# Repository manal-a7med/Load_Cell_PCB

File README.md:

# Load_Cell_PCB
HX711 Load Cell PCB Design using KiCAD 10.0

Manal Ahmed Matheen
ELECTRONICS ASSIGNMENT REPORT
Automated Food Dispensing System — Load Cell Measurement Subsystem

Task	Design Problem Statement
Domain	Embedded Systems / PCB Design
Status	Internship Technical Submission
Date	31 March 2026

Task 1 — Load Cell Selection and Key Specifications

The load cell is the primary transducer in this food dispensing system. It converts the mechanical force (weight of dispensed food) into an electrical signal. Choosing the right load cell is critical for accuracy, durability, and noise immunity in an industrial or semi-industrial environment.

1.1 Recommended Load Cell — Recommendation

✔ Selected	HX711-compatible Single-Point Load Cell (e.g., TAL220B / CZL635 / Bosche H40A) — Strain-gauge type, single-point platform cell

Reason	Strain-gauge load cells offer excellent linearity, low hysteresis, and are widely compatible with 24-bit ADC front-ends. Single-point cells are ideal for platform-style food-pan weighing.

1.2 Key Specifications to Consider

A. Load Capacity
•	Select rated capacity based on maximum expected food load plus a 20–30% safety margin.
•	For a food dispenser pan: 1 kg to 5 kg rated capacity is typical (e.g., 5 kg full-scale).
•	Overload protection rating should be ≥150% of rated capacity to survive mechanical disturbances.

B. Accuracy & Linearity
Specification targets for a reliable food-dispensing system:

Specification	Typical Requirement	Recommended Value
Non-linearity	< ±0.05% FS	< ±0.02% FS
Hysteresis	< ±0.05% FS	< ±0.02% FS
Repeatability	< ±0.05% FS	< ±0.01% FS
Temperature Effect (Zero)	< ±0.03% FS/°C	< ±0.02% FS/°C
Creep (30 min)	< ±0.03% FS	< ±0.02% FS

C. Sensitivity & Output
•	Standard bridge sensitivity: 1–3 mV/V (e.g., 2 mV/V at full rated load).
•	Bridge excitation voltage: 5V or 10V (match to ADC front-end supply).
•	Higher sensitivity = better SNR before amplification.

D. Resistance to Mechanical Disturbances
•	IP Rating: Minimum IP54 for food/dust environments; IP65 preferred.
•	Material: Aluminium alloy body (anodised) for food-grade applications; stainless steel for wet wash-down.
•	Mechanical shock rating: ≥10g or higher to withstand dispensing impacts.
•	Anti-vibration: Use rubber mounting isolators under the cell to decouple conveyor/motor vibration.

E. Electrical Noise Immunity
•	Use a 4-wire (Wheatstone bridge) or 6-wire load cell for remote sense compensation.
•	Shield the signal cable and connect the shield to a single-point earth at the MCU side.
•	Digital filtering in firmware (moving average / IIR) to suppress 50 Hz mains interference.

1.3 Comparative Summary of Load Cell Types

Type	Pros	Cons	Suitability
Strain Gauge (Single Point)	Low cost, compact, good linearity	Sensitive to off-center loads beyond cell rating	✔ Best for this application
Strain Gauge (Bending Beam)	High accuracy, robust	Larger footprint	Good alternative
Capacitive	No hysteresis, very accurate	Complex electronics, higher cost	Overkill for this use
Piezoelectric	Fast dynamic response	Cannot measure static weight accurately	✘ Not suitable

Task 2 — ADC Selection for Load Cell Signal Acquisition

Load cell output signals are extremely small (millivolt-range differential signals). A high-resolution, low-noise ADC with an integrated instrumentation amplifier front-end is required. The ADC communicates directly with the MCU.

2.1 Recommended ADC — HX711

✔ Selected	HX711 — 24-bit Sigma-Delta ADC with integrated PGA (Programmable Gain Amplifier), purpose-built for load cell / Wheatstone bridge applications

2.2 HX711 Key Specifications

Parameter	Value
Resolution	24-bit (≈16 million counts)
Input Channels	2 differential inputs (A and B)
Programmable Gain (Ch A)	128× or 64×
Programmable Gain (Ch B)	32×
Data Rate	10 SPS or 80 SPS (selectable via RATE pin)
Supply Voltage (AVDD)	2.6V – 5.5V
Supply Voltage (DVDD)	2.6V – 5.5V
Noise RMS (Ch A, Gain 128)	50 nV RMS typical
Interface	2-wire serial (PD_SCK / DOUT) — not standard SPI/I2C
Temperature Range	−40°C to +85°C
Package	SOP-16

2.3 Why HX711 Over General-Purpose ADCs
•	Integrated PGA eliminates need for an external instrumentation amplifier (reduces BOM and board space).
•	24-bit resolution provides 0.3 μV/count sensitivity at 5V excitation with gain 128 — sufficient for detecting sub-gram weight changes.
•	Differential input rejects common-mode noise from long cable runs.
•	Simple 2-wire bit-bang interface works with any MCU without SPI/I2C peripheral.
•	Low cost (~$1–2 per unit in volume), widely available, extensive community support.

2.4 Alternative High-Performance ADC — ADS1232 (Texas Instruments)

Alternative	ADS1232 — 24-bit Sigma-Delta ADC with integrated PGA, for applications requiring higher accuracy and temperature performance

Feature	HX711	ADS1232
Resolution	24-bit	24-bit
Data Rate	10 / 80 SPS	10 / 40 / 640 / 2000 SPS
Input Channels	2 differential	2 differential
Max Gain	128×	128×
Noise @ 10 SPS	~50 nV RMS	~17 nV RMS
Price (Approx.)	$1–2	$5–8
Interface	Custom 2-wire	SPI-compatible
Best For	Cost-sensitive, basic weighing	High-precision industrial weighing

For this internship system, the HX711 is the recommended choice due to its cost-effectiveness, simplicity, and adequate resolution for food dispensing applications.

Task 3 — Connectors and Cables Selection

Proper connector and cable selection is essential to maintain signal integrity for the millivolt-level load cell signals, ensure mechanical robustness, and provide EMI immunity.

3.1 Load Cell Output Cable (Load Cell → HX711/ADC)

Cable Specification

✔ Recommended	4-core shielded twisted pair (STP) cable — 24 AWG minimum, overall braid shield + foil shield, PVC or PUR jacket

Parameter	Specification
Cable Type	4-core shielded twisted pair (STP)
Conductor Gauge	24 AWG (0.205 mm²) minimum
Shielding	Braid + foil (double shield) for best EMI rejection
Jacket Material	PVC (dry environments) / PUR (wash-down / flexible routing)
Max Cable Length	≤ 3 m without additional buffering (use 6-wire for longer runs)
Color Coding (Standard)	Red=EXC+, Black=EXC−, Green=SIG+, White=SIG−, (Yellow=SEN+, Blue=SEN− for 6-wire)
Temperature Range	−20°C to +80°C

Connector at Load Cell End
•	M8 4-pin circular connector (IP65/IP67 rated) — push-pull or screw-lock.
•	Manufacturer examples: Binder Series 763, Amphenol M8, Phoenix Contact M8.
•	Use nickel-plated brass shell for corrosion resistance in food environments.

Connector at PCB/MCU End
•	Molex Micro-Fit 3.0 (2×2 or 1×4) — locking, 3A rated, vibration resistant.
•	Alternatively: JST-XH 2.54mm pitch 4-pin — lower cost, adequate for PCB prototyping.
•	For industrial boards: Phoenix Contact MSTB 2.5mm pitch screw terminal block.

3.2 HX711 → MCU Digital Interface Connections

Signal	Pin on HX711	Connector Type	Notes
PD_SCK (Clock)	Pin 11	Standard PCB header 2.54mm	Push-pull output from MCU GPIO
DOUT (Data Out)	Pin 12	Standard PCB header 2.54mm	Open-drain; add 10kΩ pull-up
VCC (DVDD)	Pin 14/15	Power header or onboard trace	3.3V or 5V from MCU regulator
GND	Pin 16	Common PCB ground	Single-point ground near ADC
AVDD (Analog)	Pin 1	Separate filtered supply	100nF + 10μF decoupling to AGND

3.3 Grounding and Shielding Best Practices
•	Connect cable shield to AGND at the PCB side only (single-point grounding prevents ground loops).
•	Separate analog ground (AGND) from digital ground (DGND); join at a single star point.
•	Route analog signal traces away from digital clock traces and switching power supply traces on the PCB.
•	Add ferrite bead (e.g., Murata BLM18AG, 600Ω @ 100MHz) on AVDD supply line to ADC.

Task 4 — Embedded Code for ADC Data Acquisition

The following code is written for the Arduino Uno (ATmega328P) MCU using the Arduino framework. It interfaces with the HX711 24-bit ADC via bit-banging the custom 2-wire serial protocol. The code includes tare (zero offset), scale calibration, moving average filtering, and serial output.

4.1 HX711 Hardware Interface Protocol
The HX711 uses a proprietary clock-gated serial protocol. When DOUT goes LOW, data is ready. The MCU generates 24 rising edges on PD_SCK to clock out 24 data bits MSB-first, followed by 1–3 additional pulses to configure channel and gain for the next conversion.

4.2 Complete Arduino Firmware

/*
 * HX711 Load Cell ADC Interface — Food Dispensing System
 * MCU: Arduino Uno (ATmega328P)
 * Author: Engineering Intern
 * Date: 2024
 */

#include <Arduino.h>

// ─── Pin Definitions ──────────────────────────────────────
#define HX711_DOUT    2    // Data Out pin (INT0 for optional interrupt use)
#define HX711_SCK     3    // Serial Clock pin

// ─── Configuration ────────────────────────────────────────
#define HX711_GAIN    1    // 1 = Ch A Gain 128 (2 pulses extra)
                           // 2 = Ch B Gain 32  (3 pulses extra)
                           // 3 = Ch A Gain 64  (4 pulses extra)
#define SAMPLES       10   // Moving average window size
#define SERIAL_BAUD   115200

// ─── Calibration Constants ────────────────────────────────
long   tareOffset  = 0;        // Set by tare() function
float  scaleGram   = 410.0f;   // Counts per gram (calibrate empirically)

// ─── Function: Read raw 24-bit signed value from HX711 ─────
long hx711_read_raw(void) {
  // Wait until data ready (DOUT goes LOW)
  while (digitalRead(HX711_DOUT) == HIGH);

  long data = 0;

  // Clock out 24 bits, MSB first
  for (uint8_t i = 0; i < 24; i++) {
    digitalWrite(HX711_SCK, HIGH);
    delayMicroseconds(1);
    data = (data << 1) | digitalRead(HX711_DOUT);
    digitalWrite(HX711_SCK, LOW);
    delayMicroseconds(1);
  }

  // Extra pulses to configure gain for next reading
  for (uint8_t i = 0; i < HX711_GAIN; i++) {
    digitalWrite(HX711_SCK, HIGH);
    delayMicroseconds(1);
    digitalWrite(HX711_SCK, LOW);
    delayMicroseconds(1);
  }

  // Sign-extend 24-bit two's complement to 32-bit
  if (data & 0x800000) {
    data |= 0xFF000000;  // Extend sign bit
  }

  return data;
}

// ─── Function: Moving Average Filter ──────────────────────
long hx711_read_average(uint8_t n) {
  long sum = 0;
  for (uint8_t i = 0; i < n; i++) {
    sum += hx711_read_raw();
  }
  return sum / n;
}

// ─── Function: Set tare (zero point) ──────────────────────
void tare(void) {
  Serial.println("Taring... ensure pan is EMPTY.");
  delay(1000);
  tareOffset = hx711_read_average(20);  // Average 20 readings for stable zero
  Serial.print("Tare offset set: ");
  Serial.println(tareOffset);
}

// ─── Function: Get weight in grams ────────────────────────
float get_weight_grams(void) {
  long raw = hx711_read_average(SAMPLES) - tareOffset;
  return (float)raw / scaleGram;
}

// ─── Function: Power down HX711 (sleep mode) ──────────────
void hx711_power_down(void) {
  digitalWrite(HX711_SCK, LOW);
  digitalWrite(HX711_SCK, HIGH);
  delayMicroseconds(65);  // Hold SCK HIGH >60μs to enter power-down
}

// ─── Function: Wake up HX711 ──────────────────────────────
void hx711_power_up(void) {
  digitalWrite(HX711_SCK, LOW);
  delay(500);  // Allow ADC to settle after wake
}

// ─── Setup ────────────────────────────────────────────────
void setup() {
  Serial.begin(SERIAL_BAUD);
  pinMode(HX711_DOUT, INPUT);
  pinMode(HX711_SCK, OUTPUT);
  digitalWrite(HX711_SCK, LOW);

  Serial.println("===================================");
  Serial.println(" Food Dispenser Load Cell System  ");
  Serial.println("===================================");
  delay(500);

  tare();  // Zero the scale on startup

  Serial.println("System ready. Monitoring weight...");
  Serial.println("-----------------------------------");
}

// ─── Main Loop ────────────────────────────────────────────
void loop() {
  float weight = get_weight_grams();

  Serial.print("Weight: ");
  Serial.print(weight, 2);
  Serial.println(" g");

  // Optional: threshold alarm for target dispensing weight
  const float TARGET_GRAMS = 200.0f;
  const float TOLERANCE    = 2.0f;

  if (weight >= (TARGET_GRAMS - TOLERANCE) &&
      weight <= (TARGET_GRAMS + TOLERANCE)) {
    Serial.println(">>> TARGET WEIGHT REACHED — Stop dispensing!");
  }

  delay(200);  // 5 Hz update rate (HX711 at 80 SPS with 10-sample average)
}

4.3 Calibration Procedure
1.	Remove all weight from the pan and power on the system.
2.	The tare() function runs automatically at startup — establishes zero reference.
3.	Place a known calibration weight (e.g., exactly 200 g certified weight) on the pan.
4.	Read the raw value via Serial Monitor.
5.	Calculate: scaleGram = raw_reading / known_weight_in_grams
6.	Update the scaleGram constant in firmware and reflash.
7.	Verify accuracy with additional reference weights across the measurement range.

4.4 Key Firmware Design Features
Feature	Implementation	Purpose
Moving Average Filter	hx711_read_average(N)	Reduce noise from vibration & EMI
Sign Extension	Two's complement 24→32 bit	Correct negative weight readings
Tare / Zero Offset	tareOffset subtraction	Compensate for pan weight
Scale Factor	Float division by scaleGram	Convert raw counts to grams
Power Management	hx711_power_down/up()	Reduce current between measurements
Target Detection	Threshold ± tolerance check	Trigger dispenser stop signal

Task 5 — PCB Design: Schematics and Board Files

The PCB integrates the HX711 ADC, power regulation, EMI filtering, MCU interface connector, and load cell connector. The design follows mixed-signal PCB best practices to ensure clean analog measurements.

5.1 PCB Design Tool Recommendation

✔ Recommended Tool	KiCad 7.0 (Open-source, professional-grade EDA) — Full schematic + PCB layout with Gerber export for manufacturing

5.2 Block-Level System Schematic Description

The schematic is organized into the following functional blocks:
•	Block 1 — Power Supply: 5V input (USB or barrel jack) → AMS1117-3.3 LDO regulator → 3.3V rail for MCU digital section. Separate ferrite-bead-isolated AVDD (5V analog) for HX711 reference input.
•	Block 2 — Load Cell Interface: M8 4-pin connector → 100nF decoupling capacitors on EXC+/EXC− → HX711 INNA/INNB inputs. Shield connected to AGND via 1MΩ resistor.
•	Block 3 — HX711 ADC: SOP-16 IC, AVDD decoupled with 10μF tantalum + 100nF MLCC. DVDD separate from AVDD with ferrite bead isolation. RATE pin tied to GND (10 SPS, lower noise mode).
•	Block 4 — MCU Interface: 4-pin 2.54mm header for DOUT, PD_SCK, VCC, GND to Arduino Uno or custom MCU board. 10kΩ pull-up on DOUT line.
•	Block 5 — Protection & Filtering: TVS diode (PRTR5V0U2X) on load cell signal lines. Common-mode choke on EXC supply lines.

5.3 Component Bill of Materials (BOM)

Ref.	Component	Value / Part No.	Package	Quantity
U1	ADC	HX711	SOP-16	1
U2	LDO Regulator	AMS1117-3.3	SOT-223	1
J1	Load Cell Connector	M8 4-pin female PCB	M8 THT	1
J2	MCU Header	Pin Header 1×4	2.54mm THT	1
J3	Power Input	Micro-USB / Barrel Jack	THT	1
C1, C2	AVDD Decoupling	10μF Tantalum	SMD 1206	2
C3–C6	Bypass Caps	100nF MLCC X7R	SMD 0402	4
R1	DOUT Pull-up	10kΩ	SMD 0402	1
R2	Shield Bleed	1MΩ	SMD 0402	1
FB1	Ferrite Bead	600Ω@100MHz (Murata BLM18AG)	SMD 0402	1
D1	ESD Protection	PRTR5V0U2X TVS	SOT-363	1

5.4 PCB Layout Guidelines

Layer Stack-up (2-layer board)
•	Top Layer (Signal): Component placement, analog signal routing, digital routing.
•	Bottom Layer (Ground Plane): Solid copper pour for GND — reduces impedance and acts as EMI shield.

Critical Routing Rules
Rule	Value / Method
Analog signal trace width	0.2 mm minimum (keep short, direct)
Digital signal trace width	0.2 mm
Power trace width	0.8 mm minimum (1.0 mm for 5V input)
Analog/Digital separation	Physical split in ground plane, joined at single star point
HX711 AVDD decoupling placement	< 3 mm from AVDD pin — C1/C2 placed first in routing
Load cell signal routing	Differential pair, matched length, away from clock traces
Trace clearance (EXC to SIG)	≥ 0.2 mm to prevent cross-talk
Silkscreen	Label all connectors, test points, and polarity markers

5.5 PCB Manufacturing Specifications

Specification	Value
Board Size	60 mm × 40 mm initially, but changed later.
Layer Count	2 (signal + ground plane)
Board Material	FR4 1.6 mm
Copper Weight	1 oz (35 μm)
Surface Finish	HASL (Hot Air Solder Level) or ENIG for fine-pitch pads
Solder Mask	Green (or blue for identification)
Silkscreen	White (both sides)
Gerber Files Required	F.Cu, B.Cu, F.Mask, B.Mask, F.SilkS, Edge.Cuts, drill file (.drl)

PLESE NOTE :-
 A barrel jack power input connector (CUI PJ-102AH) is recommended for the production version to provide a dedicated 5V supply input. In this prototype version, 5V power is supplied directly through the J2 MCU connector Pin 3.

5.6 Test Plan for PCB Validation
Visual Inspection: Check all solder joints, no shorts or bridges under magnification.

Power-On Test: Apply 5V, measure 3.3V rail (expect 3.3V ±2%), verify AVDD (expect 5V               ±1%).

HX711 Communication Test: Flash firmware, check Serial Monitor for valid (non-zero) readings.

Noise Floor Test: Short INNA/INNB inputs, record raw values — noise floor should be < ±5 counts.

Load Cell Integration Test: Connect reference load cell, apply known weights, verify accuracy.

Vibration Test: Apply mechanical disturbances, confirm moving-average filter rejects spikes.

Temperature Soak: Run at 10°C and 50°C, verify < ±0.05% FS reading drift.

References & Standards

•	HX711 Datasheet — Avia Semiconductor, Rev 1.0. 24-Bit Analog-to-Digital Converter for Weigh Scales.
•	ADS1232 Datasheet — Texas Instruments, SBAS424. 24-Bit Analog-to-Digital Converter.
•	OIML R 60 — International Recommendation for Metrological Regulation of Load Cells.
•	IEC 61000-4-5 — Electromagnetic Compatibility: Surge Immunity Requirements.
•	KiCad EDA Documentation — https://docs.kicad.org, Version 7.0.
•	Analog Devices MT-031 Tutorial — Grounding Data Converters and Solving the Mystery of 'AGND' and 'DGND'.
•	Arduino Reference Documentation — https://www.arduino.cc/reference/en/
•	Phoenix Contact MSTB Connector Series Datasheet — Phoenix Contact GmbH.

— End of Report —

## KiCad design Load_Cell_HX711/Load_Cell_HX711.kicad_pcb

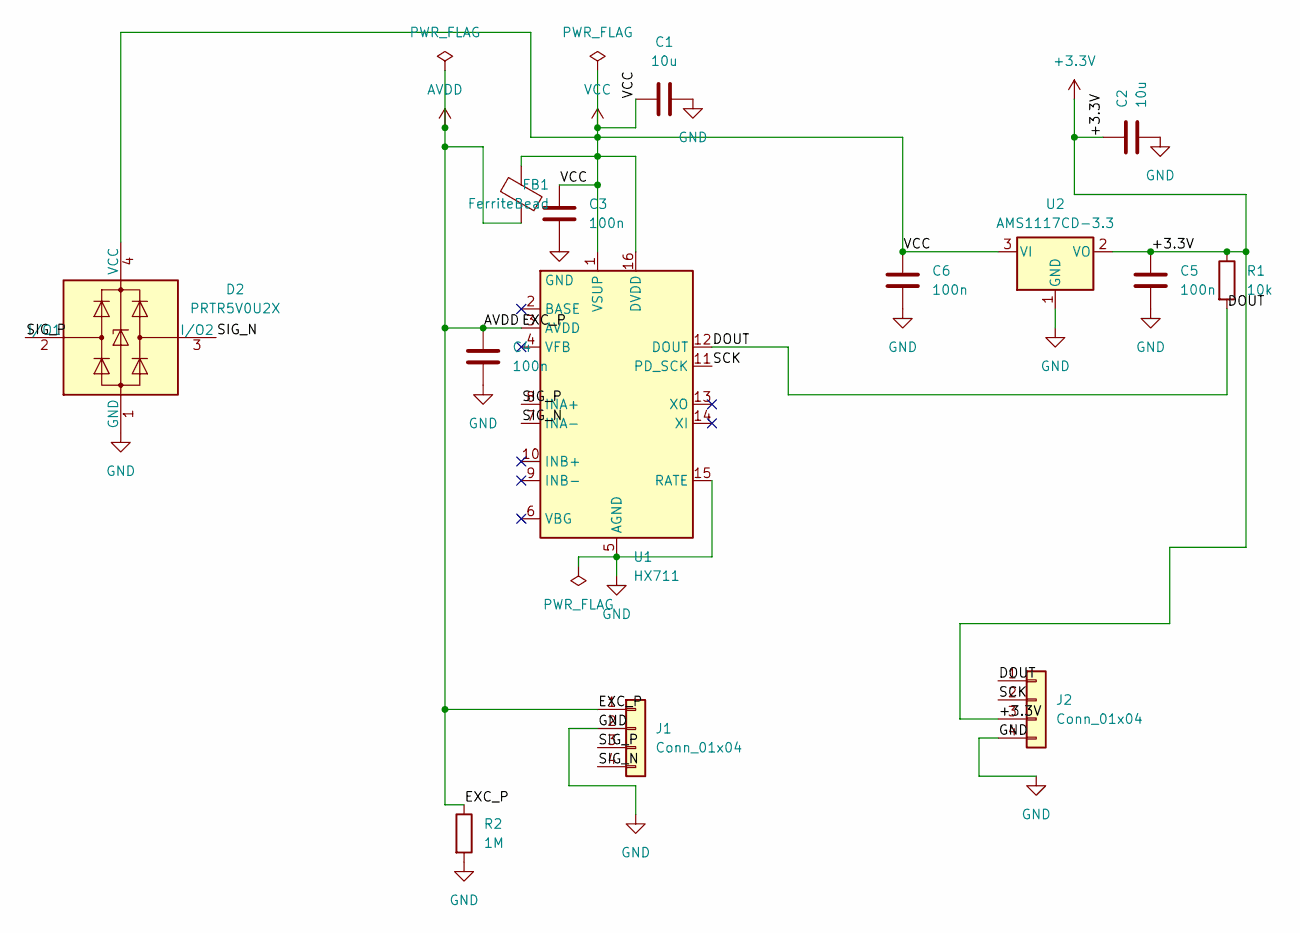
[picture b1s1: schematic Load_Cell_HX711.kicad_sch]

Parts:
C1, C2: 10u; C_1206_3216Metric
C3, C4, C5, C6: 100n; C_0402_1005Metric
D2: PRTR5V0U2X; SOT-143
FB1: FerriteBead; L_0402_1005Metric
J1, J2: Conn_01x04; FanPinHeader_1x04_P2.54mm_Vertical
R1: 10k; R_0402_1005Metric
R2: 1M; R_0402_1005Metric
U1: HX711; SOIC-16_3.9x9.9mm_P1.27mm
U2: AMS1117CD-3.3; TO-252-3_TabPin2

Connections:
+3.3V: C2.1, C5.1, J2.3, R1.1, U2.2 (VO)
/DOUT: J2.1, R1.2, U1.12 (DOUT)
/SCK: J2.2, U1.11 (PD_SCK)
/SIG_N: D2.3 (I/O2), J1.4, U1.7 (INA-)
/SIG_P: D2.2 (I/O1), J1.3, U1.8 (INA+)
AVDD: C4.1, FB1.2, J1.1, R2.1, U1.3 (AVDD)
GND: C1.2, C2.2, C3.2, C4.2, C5.2, C6.2, D2.1 (GND), J1.2, J2.4, R2.2, U1.5 (AGND), U1.15 (RATE), U2.1 (GND)
VCC: C1.1, C3.1, C6.1, D2.4 (VCC), FB1.1, U1.1 (VSUP), U1.16 (DVDD), U2.3 (VI)

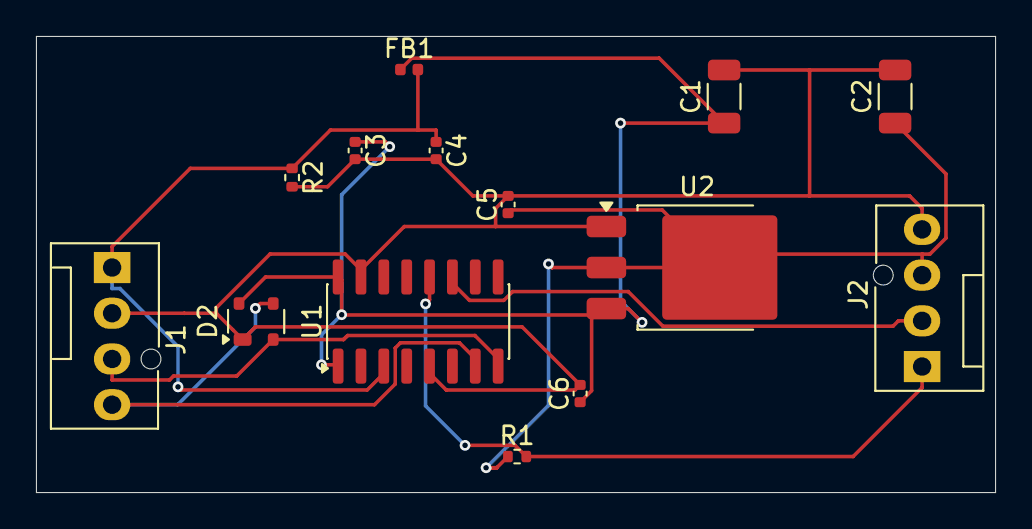
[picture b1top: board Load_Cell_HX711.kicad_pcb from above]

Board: 2 copper layers, 53.3 x 25.3 mm, 14 parts (0 on the bottom side), 8 nets.

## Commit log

2026-04-06 Report of all tasks (1-5)
2026-04-06 Update README
    Removed confidentiality notice from README.
2026-04-06 Create Load_Cell_HX711
